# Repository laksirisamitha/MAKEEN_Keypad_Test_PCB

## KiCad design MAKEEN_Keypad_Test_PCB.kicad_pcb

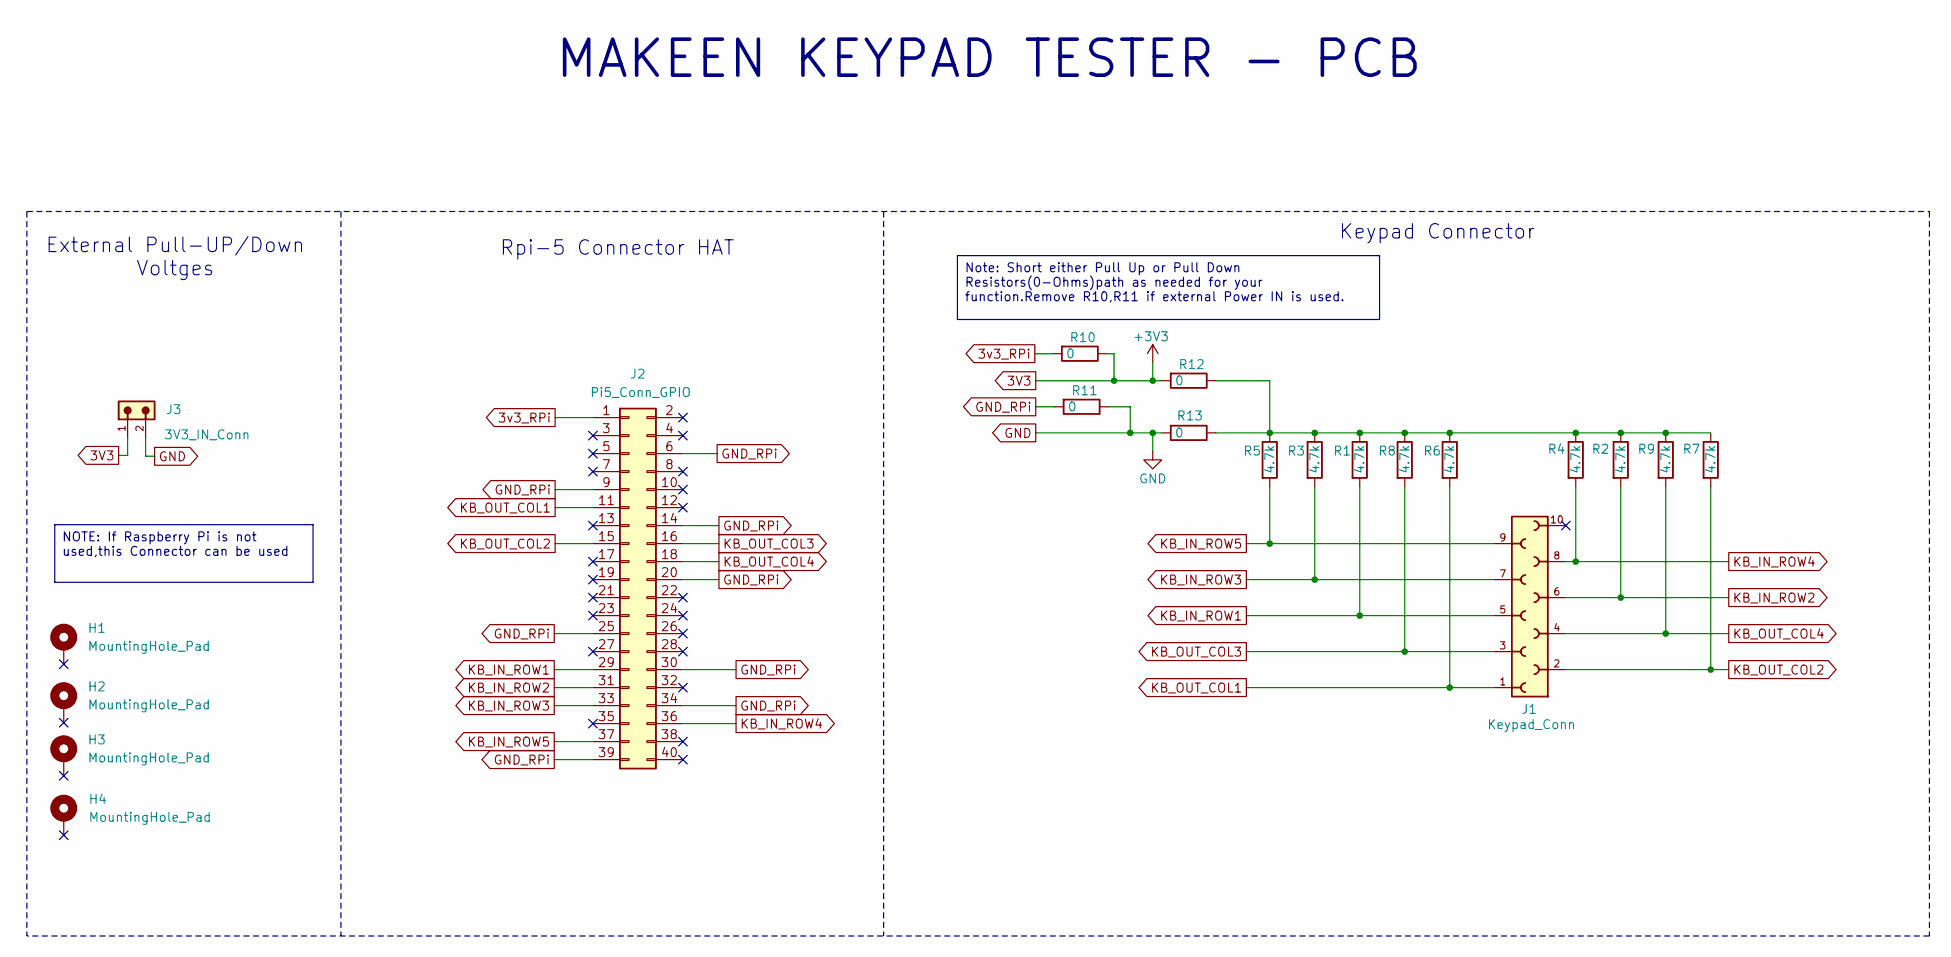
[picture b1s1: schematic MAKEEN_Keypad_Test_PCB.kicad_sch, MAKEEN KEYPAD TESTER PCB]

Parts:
H1, H2, H3, H4: MountingHole_Pad; MountingHole_2.7mm_M2.5_Pad
J1: Keypad_Conn; CONN_RCPT_10POS_0.1_SMD_690367281076
J2: Pi5_Conn_GPIO; PinSocket_2x20_P2.54mm_Vertical
J3: 3V3_IN_Conn; TERMBLOCK_2POS_5.08MM_691311500002
R1, R2, R3, R4, R5, R6, R7, R8, R9: 4.7k; R_0805_2012Metric_Pad1.20x1.40mm_HandSolder
R10, R11, R12, R13: 0; R_0805_2012Metric_Pad1.20x1.40mm_HandSolder

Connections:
3V3: J3.1, R10.1, R12.2
3v3_RPi: J2.1, R10.2
KB_IN_ROW2: J1.6, J2.31, R2.2
GND: J3.2, R11.1, R13.2
GND_RPi: J2.6, J2.9, J2.14, J2.20, J2.25, J2.30, J2.34, J2.39, R11.2
KB_IN_ROW1: J1.5, J2.29, R1.2
KB_IN_ROW3: J1.7, J2.33, R3.2
KB_IN_ROW4: J1.8, J2.36, R4.2
KB_IN_ROW5: J1.9, J2.37, R5.2
KB_OUT_COL1: J1.1, J2.11, R6.2
KB_OUT_COL2: J1.2, J2.15, R7.2
KB_OUT_COL3: J1.3, J2.16, R8.2
KB_OUT_COL4: J1.4, J2.18, R9.2
unnamed: R1.1, R2.1, R3.1, R4.1, R5.1, R6.1, R7.1, R8.1, R9.1, R12.1, R13.1

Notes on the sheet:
Keypad Connector
External Pull-UP/Down Voltges
MAKEEN KEYPAD TESTER - PCB
Rpi-5 Connector HAT
Note: Short either Pull Up or Pull Down Resistors(0-Ohms)path as needed for your function.Remove R10,R11 if external Power IN is used.
NOTE: If Raspberry Pi is not used,this Connector can be used

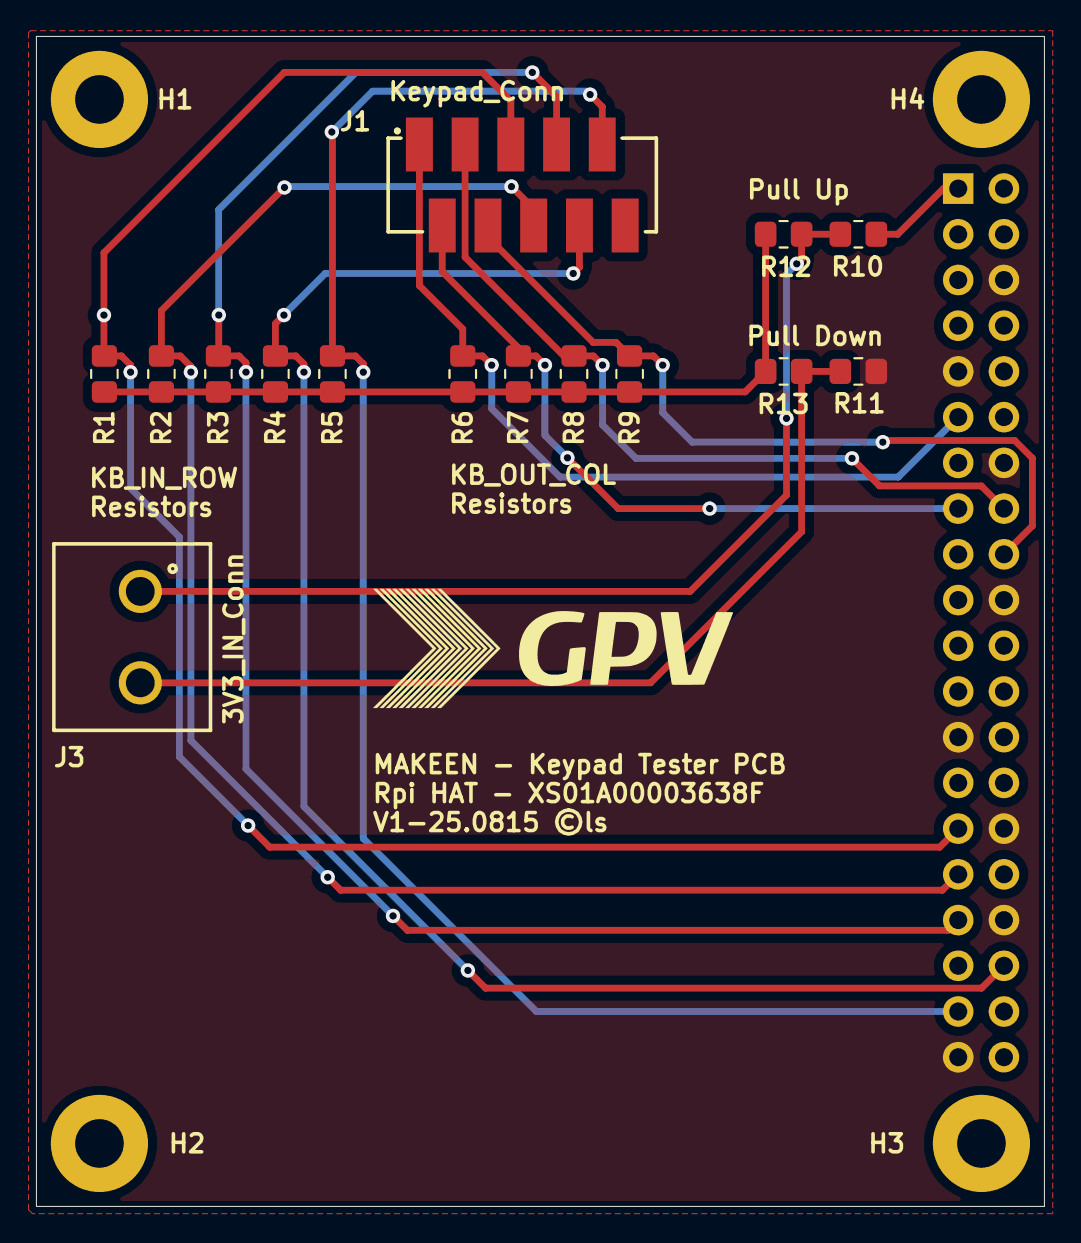
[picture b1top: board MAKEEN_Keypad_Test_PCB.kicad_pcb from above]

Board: 2 copper layers, 56.0 x 65.0 mm, 20 parts (1 on the bottom side), 14 nets.

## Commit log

2025-08-15 Routing
2025-08-15 V1-completed
2025-08-15 V1-Gerbers added

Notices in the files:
MAKEEN_Keypad_Test_PCB.kicad_pcb:
©laksirisamitha
V1-25.0815 ©ls
